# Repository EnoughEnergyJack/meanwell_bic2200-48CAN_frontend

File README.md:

# Meanwell BIC2200 Front-End Controller

- Many companies develop things that are critical for development, but are not needed for their products/IP. This is one of those developments.
- It is a front-end PCB/Screen that allows you to control the Meanwell BIC2200-48CAN as if it were a Bench PSU, very simple, mostly generated by AI prompts.
- The psu itself is great because it is bidirectional, you can set it as a supply or a regenerative load, up to ~2.2kW.
- If this is useful to you, give Enough Energy Ltd a shoutout, but to be clear this was mostly a "quick and dirty"(but very effective) PCB to help our other developments along.

## Features

- **Display Modes**
  - Main display: Real-time voltage, current, power, and energy monitoring
  - Limits display: Voltage and current setpoint configuration
  
- **Controls**
  - Rotary encoders for voltage (38-65V) and current (0-45A positive, -38A to 0A negative) adjustment
  - Dedicated buttons for output control, view switching, and setpoint confirmation
  
- **Real-Time Monitoring**
  - Output voltage and current readings
  - Power consumption (watts)
  - Energy consumption tracking (watt-hours)
  - Runtime timer
  - Output status indicator
  
- **CAN Bus Communication**
  - Bidirectional communication with Meanwell power supply
  - Automatic setpoint echo verification
  - Real-time data polling

## Hardware

The project uses a dedicated PCB designed specifically for the Arduino Uno. The PCB integrates all required hardware components:

- **16x4 Character LCD Display** (HD44780-compatible)
- **2x Rotary Encoders** with integrated push buttons (voltage and current adjustment)
- **4x Push Buttons** (VIEW, CHNG I, SET BUFFER, OUTPUT)
- **MCP2515 CAN Controller** with CAN transceiver
- **Power Input** (barrel jack connector)
- **Pin Headers** for Arduino Uno connection
- **CAN Bus Connector** for power supply communication

### Wiring Harness

For wiring harness details and external connections, refer to the schematic in the documentation:
- **Schematic**: See `Documentation/Meanwell_FE v17.pdf` for complete wiring diagrams and harness specifications

The PCB is designed to mount directly onto an Arduino Uno, with all components and connections pre-routed on the board.

## Software Dependencies

### Arduino Libraries
- `LiquidCrystal` - LCD display control (included with Arduino IDE)
- `mcp_can` - MCP2515 CAN controller library
- `SPI` - SPI communication (included with Arduino IDE)
- `Encoder` - Rotary encoder input handling

### Installation

1. Install the required libraries via Arduino Library Manager:
   ```
   - mcp_can (by Seeed Studio or compatible)
   - Encoder (by Paul Stoffregen)
   ```

2. Clone or download this repository.

3. Mount the dedicated PCB onto your Arduino Uno (see schematic for pin alignment)

4. Connect the wiring harness as specified in the schematic (`Documentation/Meanwell_FE v17.pdf`)

5. Open `Meanwell/Meanwell.ino` in the Arduino IDE

6. Configure pin assignments in `Meanwell/config.h` if needed (defaults should work with the PCB)

7. Upload the firmware to your Arduino board

## Pin Configuration

Default pin assignments (defined in `config.h`):

| Component | Pin | Description |
|-----------|-----|-------------|
| LCD RS | A2 | Register select |
| LCD EN | A3 | Enable |
| LCD D4-D7 | 5, 4, 3, A4 | Data lines (4-bit mode) |
| Voltage Encoder CLK | 6 | Clock pin |
| Voltage Encoder DT | 7 | Data pin |
| Current Encoder CLK | A0 | Clock pin |
| Current Encoder DT | 9 | Data pin |
| SET BUF Button | A1 | Set buffer values |
| OP TOGGLE Button | A5 | Output enable/disable |
| VIEW Button | 8 | Display mode toggle |
| CHNG I Button | 2 | Current direction toggle |
| CAN CS | 10 | CAN controller chip select |

## Usage

### Basic Operation

1. **Setting Voltage and Current Limits**
   - Press VIEW to enter Limits Display mode
   - Rotate voltage encoder to set desired voltage (38-65V)
   - Rotate current encoder to set positive current limit (0-45A)
   - Press CHNG I to switch to negative current editing
   - Rotate current encoder to set negative current limit (-38A to 0A)
   - Press SET BUF to apply settings to the power supply

2. **Enabling Output**
   - Configure desired limits (see above)
   - Press OP TOGGLE to enable output
   - Monitor real-time values on Main Display

3. **Monitoring**
   - Main Display shows:
     - Output voltage (V)
     - Output current (A)
     - Power consumption (W)
     - Energy consumed (Wh)
     - Runtime timer (seconds)
     - Output status (ON/OFF)

For detailed user instructions, see [USER_GUIDE.md](USER_GUIDE.md).

## Technical Details

### CAN Communication

- **Baud Rate**: 250 kbps
- **CAN ID TX**: 0xC0300 (commands to power supply)
- **CAN ID RX**: 0x800C0200 (responses from power supply)
- **Protocol**: PMBus-compatible commands over CAN
- **Mechanism**: Request-response pattern (see [CAN Messaging Protocol](Documentation/CAN_MESSAGING.md) for details)

- Voltage setpoint (CMD_VOUT_SET: 0x20)
- Current setpoint (CMD_IOUT_SET: 0x30)
- Reverse current setpoint (CMD_REVERSE_IOUT_SET: 0x130)
- Output enable/disable (CMD_OPERATION: 0x00)
- Read voltage (CMD_READ_VOUT: 0x60)
- Read current (CMD_READ_IOUT: 0x61)

### Display Update Rates

- Main Display: 20 Hz (50ms intervals)
- Limits Display: 2 Hz (500ms intervals)
- CAN polling: 10 Hz (100ms intervals)

### Energy Tracking

- Energy meter resets when output is enabled
- Power calculation uses filtered values for stability
- Energy integration: `E = ∫ P dt` (watt-hours)

## Development

### Building

1. Ensure all required libraries are installed
2. Open `Meanwell/Meanwell.ino` in Arduino IDE
3. Select your board and port
4. Compile and upload

### Debugging

- Serial output available at 115200 baud
- CAN communication status indicated by blinking `[ ]` on display
- Setpoint echo verification ensures commands are received

## Documentation

- [User Guide](USER_GUIDE.md) - Complete user manual
- [CAN Messaging Protocol](Documentation/CAN_MESSAGING.md) - Detailed explanation of the request-response CAN communication mechanism
- [Documentation/](Documentation/) - Hardware datasheets and specifications
- [MEANWELL.dbc](Documentation/MEANWELL.dbc) - CAN bus DBC file for protocol reference

## License

MIT

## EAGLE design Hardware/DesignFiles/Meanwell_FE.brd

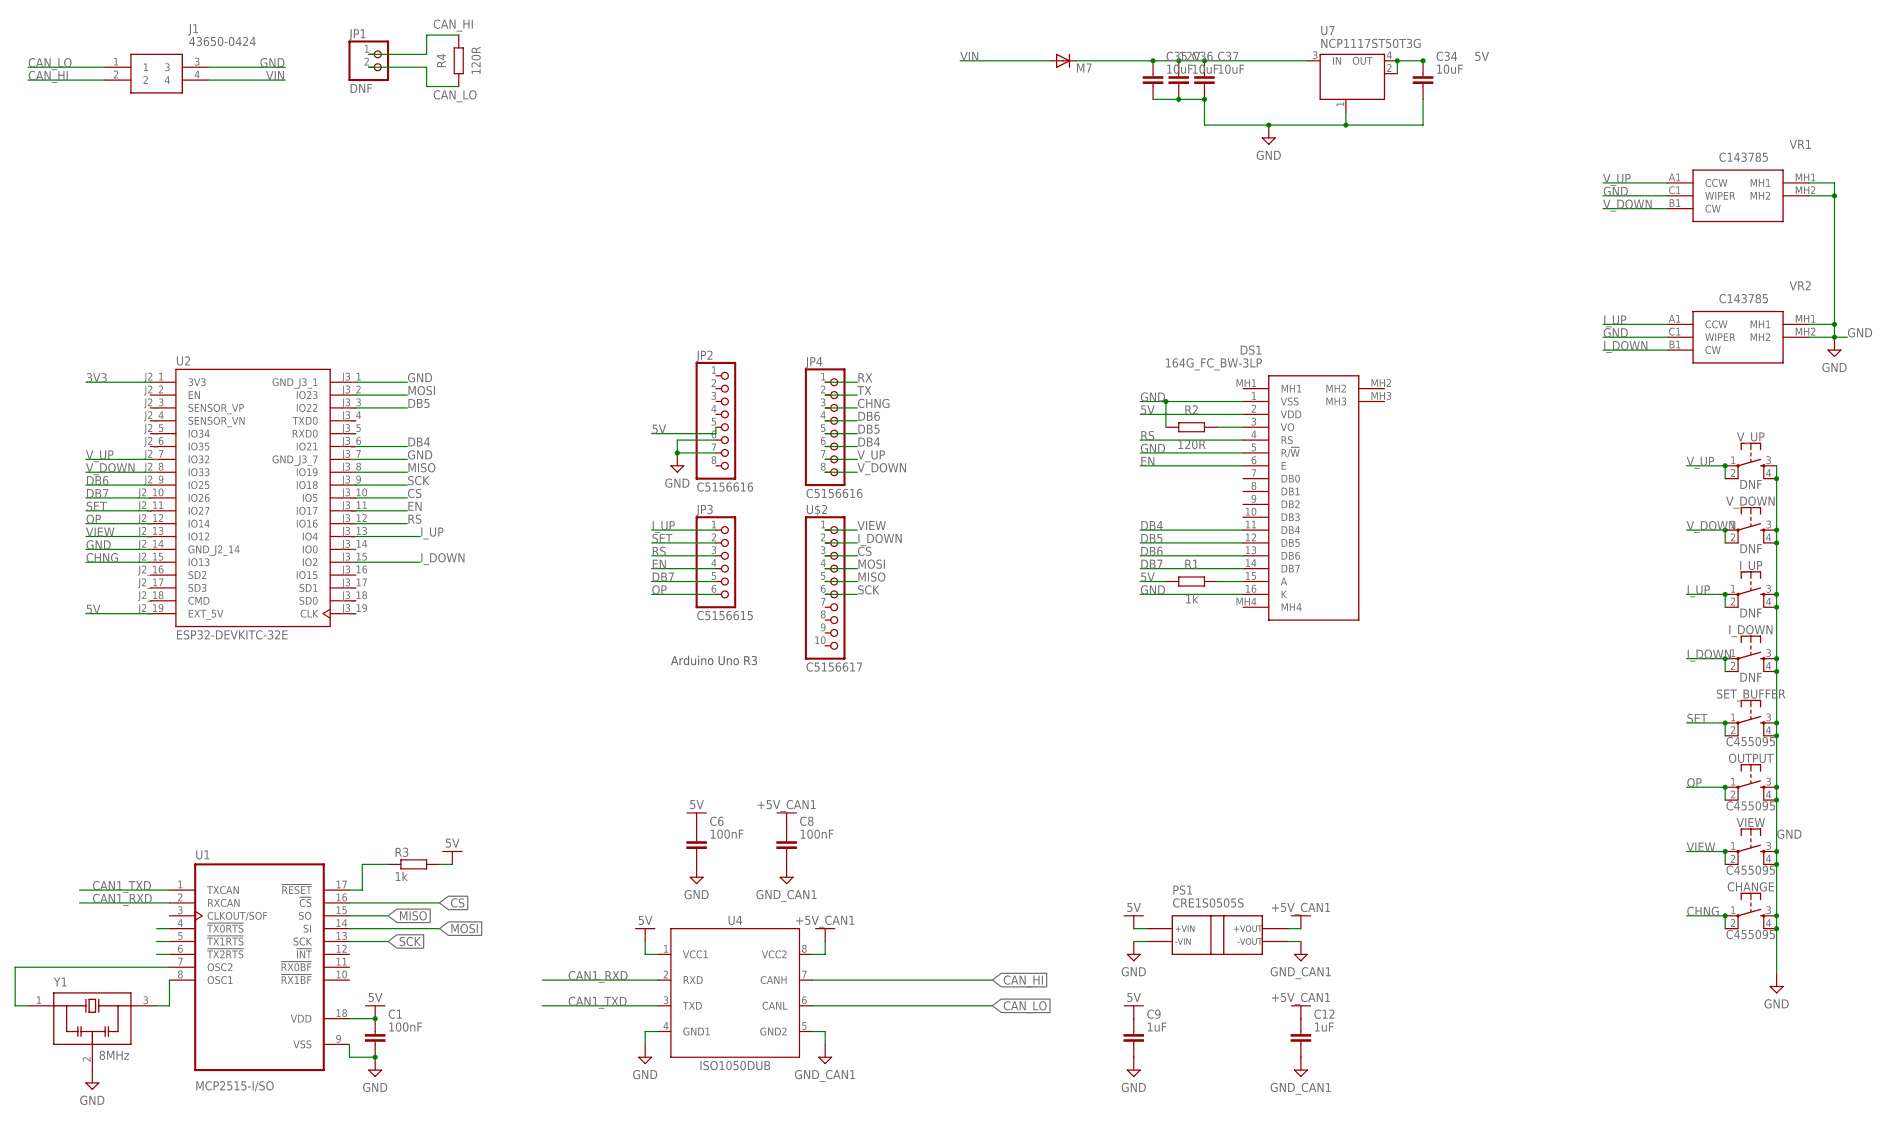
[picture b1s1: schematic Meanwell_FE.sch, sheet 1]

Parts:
C1, C6, C8: 100nF; CAPC1608X85
C9, C12: 1uF; CAPC1608X85
C34, C35, C36, C37: 10uF; CAPC2012X110
CHANGE: C455095; SWITCH-MOMENTARY-PTH-6.5MM
D1: M7; SMB
DS1: 164G_FC_BW-3LP; 164GFCBW3LP
I_DOWN: DNF; SWITCH-MOMENTARY-PTH-6.5MM
I_UP: DNF; SWITCH-MOMENTARY-PTH-6.5MM
J1: 43650-0424; 43650-04YY_242526
JP1: DNF; 1X02
JP2, JP4: C5156616; 1X08-BIG
JP3: C5156615; 1X06-BIG
OUTPUT: C455095; SWITCH-MOMENTARY-PTH-6.5MM
PS1: CRE1S0505S; CRE1(SC)
R1, R3: 1k; RESC1608X60
R2, R4: 120R; RESC1608X60
SET_BUFFER: C455095; SWITCH-MOMENTARY-PTH-6.5MM
U1: MCP2515-I/SO; SOIC127P1030X265-18N
U2: ESP32-DEVKITC-32E; MODULE_ESP32-DEVKITC-32E
U4: ISO1050DUB; SOP254P1040X485-8
U7: NCP1117ST50T3G; SOT223
U$2: C5156617; 1X10-BIG
VIEW: C455095; SWITCH-MOMENTARY-PTH-6.5MM
VR1, VR2: C143785; PEC12R4215FN0024
V_DOWN: DNF; SWITCH-MOMENTARY-PTH-6.5MM
V_UP: DNF; SWITCH-MOMENTARY-PTH-6.5MM
Y1: 8MHz; OSC_CSTNE8M00GH5C000R0

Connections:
3V3: U2.J2_1 (3V3)
5V: C1.1, C6.1, C9.1, C34.1, DS1.2 (VDD), JP2.5, PS1.2 (+VIN), R1.1, R3.2, U1.18 (VDD), U2.J2_19 (EXT_5V), U4.1 (VCC1), U7.2 (OUT), U7.4 (OUT)
12V: C35.1, C36.1, C37.1, D1.C, U7.3 (IN)
+5V_CAN1: C8.1, C12.1, PS1.4 (+VOUT), U4.8 (VCC2)
CAN1_RXD: U1.2 (RXCAN), U4.2 (RXD)
CAN1_TXD: U1.1 (TXCAN), U4.3 (TXD)
CAN_HI: J1.2, JP1.1, R4.2, U4.7 (CANH)
CAN_LO: J1.1, JP1.2, R4.1, U4.6 (CANL)
CHNG: CHANGE.1, CHANGE.2, JP4.3, U2.J2_15 (IO13)
CS: U1.16 (!CS), U2.J3_10 (IO5), U$2.3
DB4: DS1.11 (DB4), JP4.6, U2.J3_6 (IO21)
DB5: DS1.12 (DB5), JP4.5, U2.J3_3 (IO22)
DB6: DS1.13 (DB6), JP4.4, U2.J2_9 (IO25)
DB7: DS1.14 (DB7), JP3.5, U2.J2_10 (IO26)
EN: DS1.6 (E), JP3.4, U2.J3_11 (IO17)
GND: C1.2, C6.2, C9.2, C34.2, C35.2, C36.2, C37.2, CHANGE.3, CHANGE.4, DS1.1 (VSS), DS1.5 (R/!W), DS1.16 (K), I_DOWN.3, I_DOWN.4, I_UP.3, I_UP.4, J1.3, JP2.6, JP2.7, OUTPUT.3, OUTPUT.4, PS1.1 (-VIN), R2.1, SET_BUFFER.3, SET_BUFFER.4, U1.9 (VSS), U2.J2_14 (GND_J2_14), U2.J3_1 (GND_J3_1), U2.J3_7 (GND_J3_7), U4.4 (GND1), U7.1 (GND/ADJ), VIEW.3, VIEW.4, VR1.C1 (WIPER), VR1.MH1, VR1.MH2, VR2.C1 (WIPER), VR2.MH1, VR2.MH2, V_DOWN.3, V_DOWN.4, V_UP.3, V_UP.4, Y1.2 (GND)
GND_CAN1: C8.2, C12.2, PS1.3 (-VOUT), U4.5 (GND2)
I_DOWN: I_DOWN.1, I_DOWN.2, U2.J3_15 (IO2), U$2.2, VR2.B1 (CW)
I_UP: I_UP.1, I_UP.2, JP3.1, U2.J3_13 (IO4), VR2.A1 (CCW)
MISO: U1.15 (SO), U2.J3_8 (IO19), U$2.5
MOSI: U1.14 (SI), U2.J3_2 (IO23), U$2.4
unnamed: DS1.3 (VO), R2.2
unnamed: U1.7 (OSC2), Y1.1 (IN)
unnamed: DS1.15 (A), R1.2
unnamed: R3.1, U1.17 (!RESET)
unnamed: U1.8 (OSC1), Y1.3 (OUT)
OP: JP3.6, OUTPUT.1, OUTPUT.2, U2.J2_12 (IO14)
RS: DS1.4 (RS), JP3.3, U2.J3_12 (IO16)
RX: JP4.1
SCK: U1.13 (SCK), U2.J3_9 (IO18), U$2.6
SET: JP3.2, SET_BUFFER.1, SET_BUFFER.2, U2.J2_11 (IO27)
TX: JP4.2
VIEW: U2.J2_13 (IO12), U$2.1, VIEW.1, VIEW.2
VIN: D1.A, J1.4
V_DOWN: JP4.8, U2.J2_8 (IO33), VR1.B1 (CW), V_DOWN.1, V_DOWN.2
V_UP: JP4.7, U2.J2_7 (IO32), VR1.A1 (CCW), V_UP.1, V_UP.2

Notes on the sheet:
Arduino Uno R3

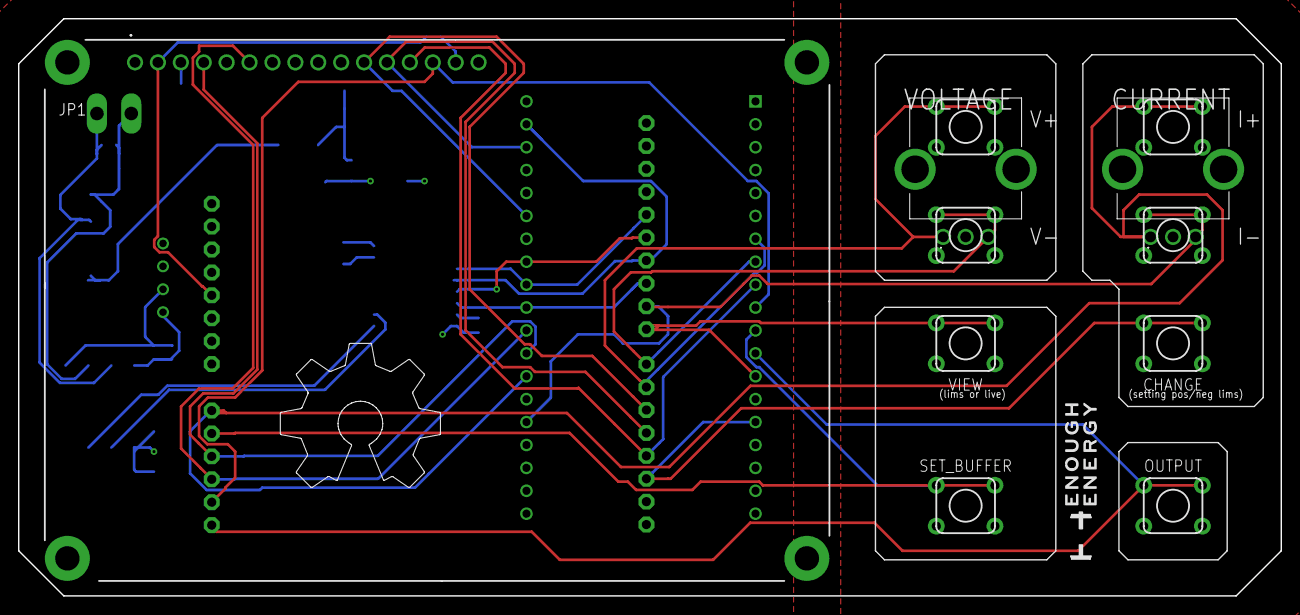
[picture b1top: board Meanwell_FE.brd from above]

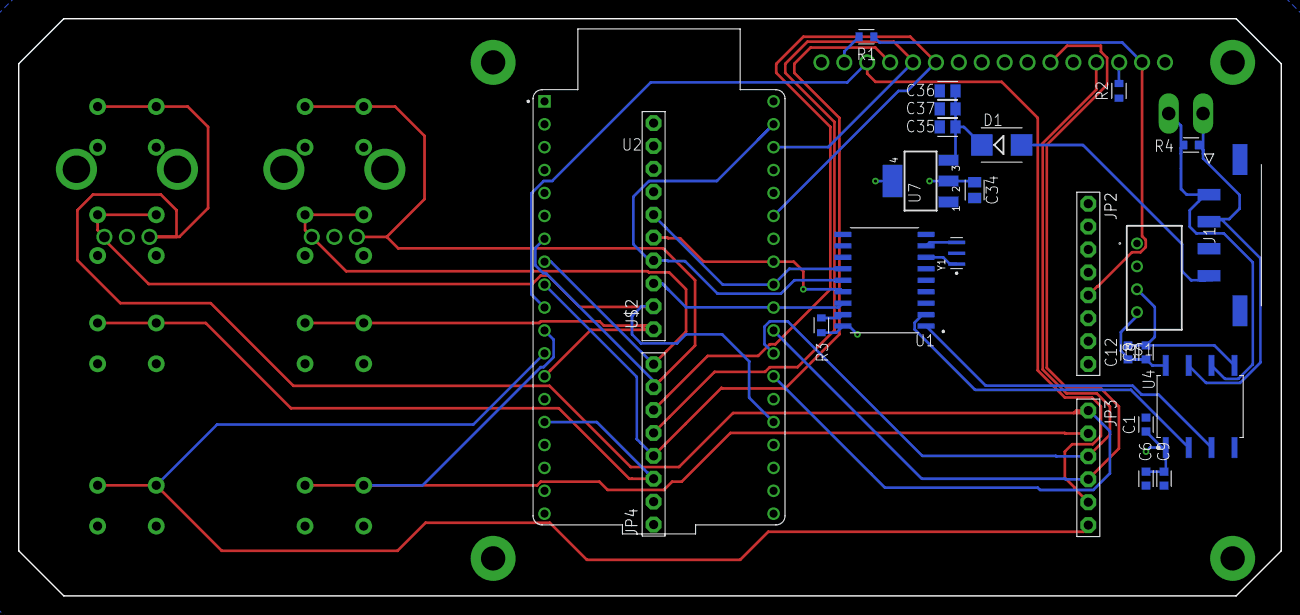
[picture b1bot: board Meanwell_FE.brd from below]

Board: 2 copper layers, 140.0 x 64.0 mm, 37 parts (25 on the bottom side), 33 nets.

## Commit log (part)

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2025-12-07 Uploading the hardware files.
2025-12-07 Rename Meanwell_FE.f3z to Hardware/DesignFiles/Meanwell_FE.f3z
2025-12-07 Rename Meanwell_FE.brd to Hardware/DesignFiles/Meanwell_FE.brd
2025-12-07 Rename Meanwell_FE.fbrd to Hardware/DesignFiles/Meanwell_FE.fbrd
2025-12-07 Rename Meanwell_FE.fsch to Hardware/DesingFiles/Meanwell_FE.fsch
2025-12-07 Rename Meanwell_FE.sch to Hardware/DesignFiles/Meanwell_FE.sch
2025-12-07 Rename Meanwell_FE_v26_JLCBOM_2025-12-06-JLCPCB Assembly Order.xls to Hardware/Release/Meanwell_FE_v26_JLCBOM_2025-12-06-JLCPCB Assembly Order.xls
2025-12-07 Rename Meanwell_FE.fsch to Meanwell_FE.fsch
2025-12-07 Rename Meanwell_FE_v26_JLC_PCB.zip to Hardware/Release/Meanwell_FE_v26_JLC_PCB.zip
2025-12-07 Rename display.h to display.h
2025-12-07 Rename Hardware/MEANWELL BRACKET v3.stl to Hardware/Mechanical/MEANWELL BRACKET v3.stl
2025-12-07 Rename Hardware/MEANWELL BRACKET.f3d to Hardware/Mechanical/MEANWELL BRACKET.f3d
2025-12-07 Rename Hardware/MEANWELL BRACKET_SMALL v3.stl to Hardware/Mechanical/MEANWELL BRACKET_SMALL v3.stl
